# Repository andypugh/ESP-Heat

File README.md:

ESP32 Heating Controller
==============

A multi-zone central heating controller based on the ESP32.

It can be configured for an almost unlimited number of zones, pumps and separate boilers.
Boiler run-on is supported, and configurable. 
Temperature sensing assumes DS18B20 sensors. 
One zone per valve, and it is assumed that zone valves trip microswitches when open. 
 
Branches: 
no_master: Uses GPIO to read from the DS18B20 sensors

master: using a DS2482 1-wire master adaptor for longer cable runs. Using WebServer
to handle http requests. 

WiFiServer: Initial version using wiFi server and parsing incoming URLs byte-by-byte
 
The DS2482-100 is a I2C->1-Wire bridge (http://www.maximintegrated.com/datasheet/index.mvp/id/4382),
contains functionality that means it is better at driving long and complex networks. 

I used a DS2482-800 which additionally expands the bus to 8 separate channels, which allows
for longer single-ended networks.
For simplicity, using this break-out board. 
https://uk.rs-online.com/web/p/communication-wireless-development-tools/1360731/

Here is the main screen, showing a diagram of the house, with the temperature of each zone. 
The shape and position of each room is defined by an SVG path, for example:
"M250 350 v190 h140 v-190 z"
So that almost any house layout (or limited graphical elements for tanks etc) can be defined. 

<kbd></kbd>

Here is one of the programming screens

<kbd></kbd>

And the setup screen where the pins for each valve and pump etc can be defined, as well
as the house layout and the temperature sensor allocation. 

<kbd></kbd>

And here is one iteration of the hardware installed in a consumer unit case with
Neutrik connectors for the pumps and valves and CB connectors for the temperature sensors:

<kbd></kbd>

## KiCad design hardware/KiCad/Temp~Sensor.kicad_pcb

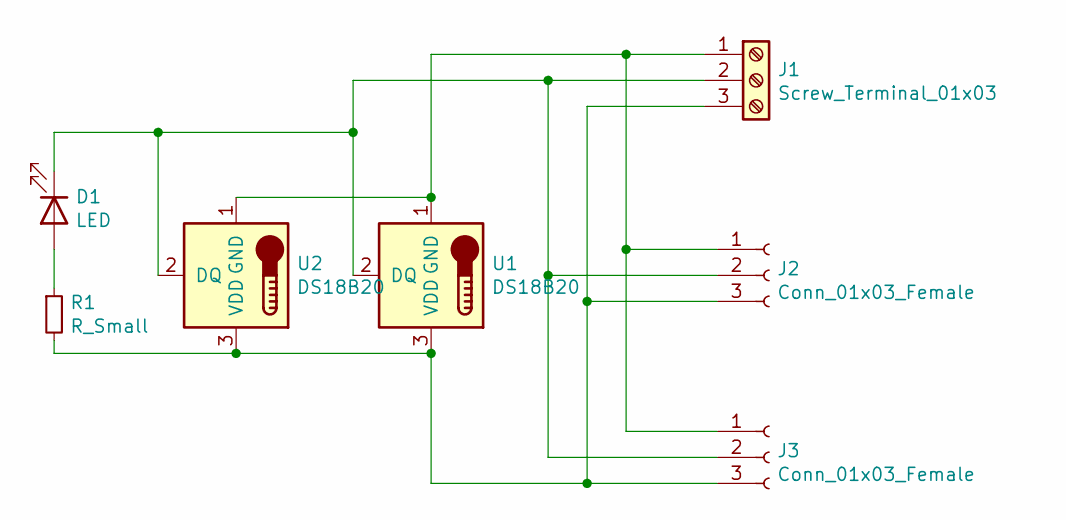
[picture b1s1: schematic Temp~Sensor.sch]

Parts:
D1: LED; LED_0603_HandSoldering
J1: Screw_Terminal_01x03; PhoenixContact_MCV-G_03x3.50mm_Vertical
J2: Conn_01x03_Female; Amphenol_FCI_3
J3: Conn_01x03_Female; RSProClamp
R1: R_Small; R_0603_HandSoldering
U1, U2: DS18B20; TO-92_Molded_Wide_Reverse

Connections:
unnamed: D1.1 (K), J1.2, J2.2, J3.2, U1.2 (DQ), U2.2 (DQ)
unnamed: D1.2 (A), R1.1
unnamed: J1.1, J2.1, J3.1, U1.1 (GND), U2.1 (GND)
unnamed: J1.3, J2.3, J3.3, R1.2, U1.3 (VDD), U2.3 (VDD)

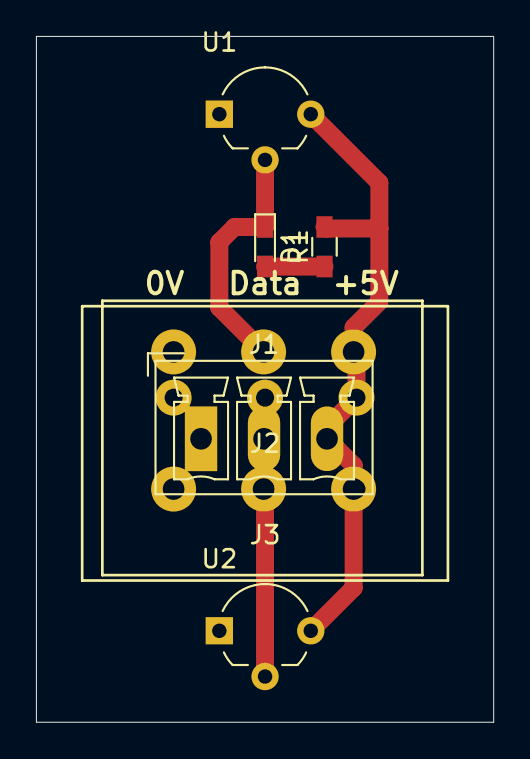
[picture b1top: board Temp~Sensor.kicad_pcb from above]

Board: 2 copper layers, 25.4 x 38.1 mm, 7 parts (0 on the bottom side), 4 nets.

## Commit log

2020-10-30 change author name
2020-10-30 Add the README and LICENSE
2020-10-30 Add screenshot
2020-10-30 Try to fix screenshot link
2020-11-07 prepare to use DS2842 one-wire master
2020-11-08 Switch to using DS2482-800 1-wire hub
2020-11-14 Wired up, nearly working
2020-11-15 Add led blnk error codes
2020-11-15 switch back to WiFiServer for this branch
2020-11-20 Restuctured to use WebServer rather than WiFiServer
2020-11-22 Move config data to a header file
2020-11-24 Create sample credentials.h file
    This will need to be configured to suit your setup.
    If the error_email is a null string ("\0") then error email sending will be disabled
2020-12-01 Update README.md
    Add hardware photo
2020-12-01 Add files via upload
    Add the photo
2020-12-17 Allow zone temperature to be set by a URL request for example by a remote ESP32. Also allow error modes to heal
2020-12-17 Send emails on error conditions
2020-12-17 Move GetTemperatures() so that all channels are updated. Also list addresses of found sensors
2020-12-27 Correct bacdly merged README
2021-04-29 various updates
2021-10-18 Add external IP to notifications. Add reset magig-URL
2021-10-28 Add a settings screen
2021-10-28 Major refactor. Zones, pumps, boilers as structs. Broken into many files
2021-10-30 Setting screen now works, except for zone names
2021-10-30 Zone names fixed. Floorplan still needs doing
2021-10-30 Fix typos in DS2482 mode
2021-10-31 Add boiler feed and return sensor handling
2021-11-02 Update to AsynchWebServer and ESP_Mail_Client
2021-11-02 Fix unit swapping
2021-11-03 set up OTA (Over the Air flashing) for remote software updating
2021-11-16 Attempt to improve sensor error handling Also switch to using clock time for timeouts.
2021-11-16 Add PCB and 3D model files
2021-12-26 Zone active bit was set wrongly
2022-07-15 Add relay control to power-off reset the temperature sensors
2022-07-15 Add email subject to credentials
2022-07-15 add http authentication data to credentials
2022-07-15 Add minimal http security (password)
2022-07-17 Add a pin to power-of reset the OneWire hub
2022-07-17 Set unused pins to a default state
2022-07-18 Fix default pin init bug
2022-07-18 Flip default states
2022-07-18 Pinouts of controller and ESP32
2022-07-18 Rework DS2482 reset. Add timeout info. Deboince programmingn URLS
2022-07-20 Implement SVG paths for room outlines
2022-07-20 Improve readme formatting and typos
2022-07-20 Improve readme formatting
2022-10-18 Use AP mode to define credentials. Re-arrange programming screen
2022-10-22 Found on Eris...
2022-10-23 Fix resetting of bitmasks, make network settings available outside AP mode
2022-10-24 revert something odd in a merge
2022-10-24 Remove debug line
2023-10-19 Slaithwite 221024
2023-10-26 added time arrow
2023-10-26 Attempt to improve default-on behaviour with faulted sensors
2023-10-26 Fix default behaviour some more
2025-01-11 Add ESP8266/DHT11 sensor
